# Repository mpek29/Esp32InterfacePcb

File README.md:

# Esp32InterfacePcb

# UsbUartBridge

## 🚀 Overview

**Esp32InterfacePCB** is an open-source PCB designed to provide a reliable interface between an **Espressif ESP32-WROOM-32E** module and various external modules using **JST-SM & JST-SH connectors**. This PCB simplifies ESP32 integration into embedded, IoT, and home automation projects.

## 🎯 Purpose

- 🔌 **Modular Interface**: Facilitates the connection between an ESP32-WROOM-32E and other peripherals.
- 📏 **Compact & Optimized Design**: Suitable for embedded project constraints.
- 🛠️ **Open-source & Customizable**: Modify and adapt the design to fit your specific needs.

## 📝 Features

| 🏷️ Feature            | 🔍 Description                                                 |
| ---------------------- | -------------------------------------------------------------- |
| 🔌 **ESP32 Interface** | Compatible with the ESP32-WROOM-32E module                     |
| 📡 **Connectors**      | JST-SM & JST-SH for easy connections                           |
| ⚡ **Power Supply**     | Supports 3.3V                                                  |
| 🛠️ **GPIO Access**    | Access to key GPIO pins for seamless integration               |
| 🔧 **Capacitors**      | Decoupling capacitors for signal stability                     |
| 🖥️ **PCB Design**     | Open-source & customizable                                     |
| 🌍 **Use Cases**       | IoT, embedded systems, automation, robotics, rapid prototyping |

## 📐 PCB Design Preview
| 📜 Schematic | 🖥️ PCB Layout | 🏗️ 3D |
|-----------|-----------|-----------|
|  |  |  |

## 🌟 License

This project is open-source. Feel free to use, modify, and contribute! 🚀

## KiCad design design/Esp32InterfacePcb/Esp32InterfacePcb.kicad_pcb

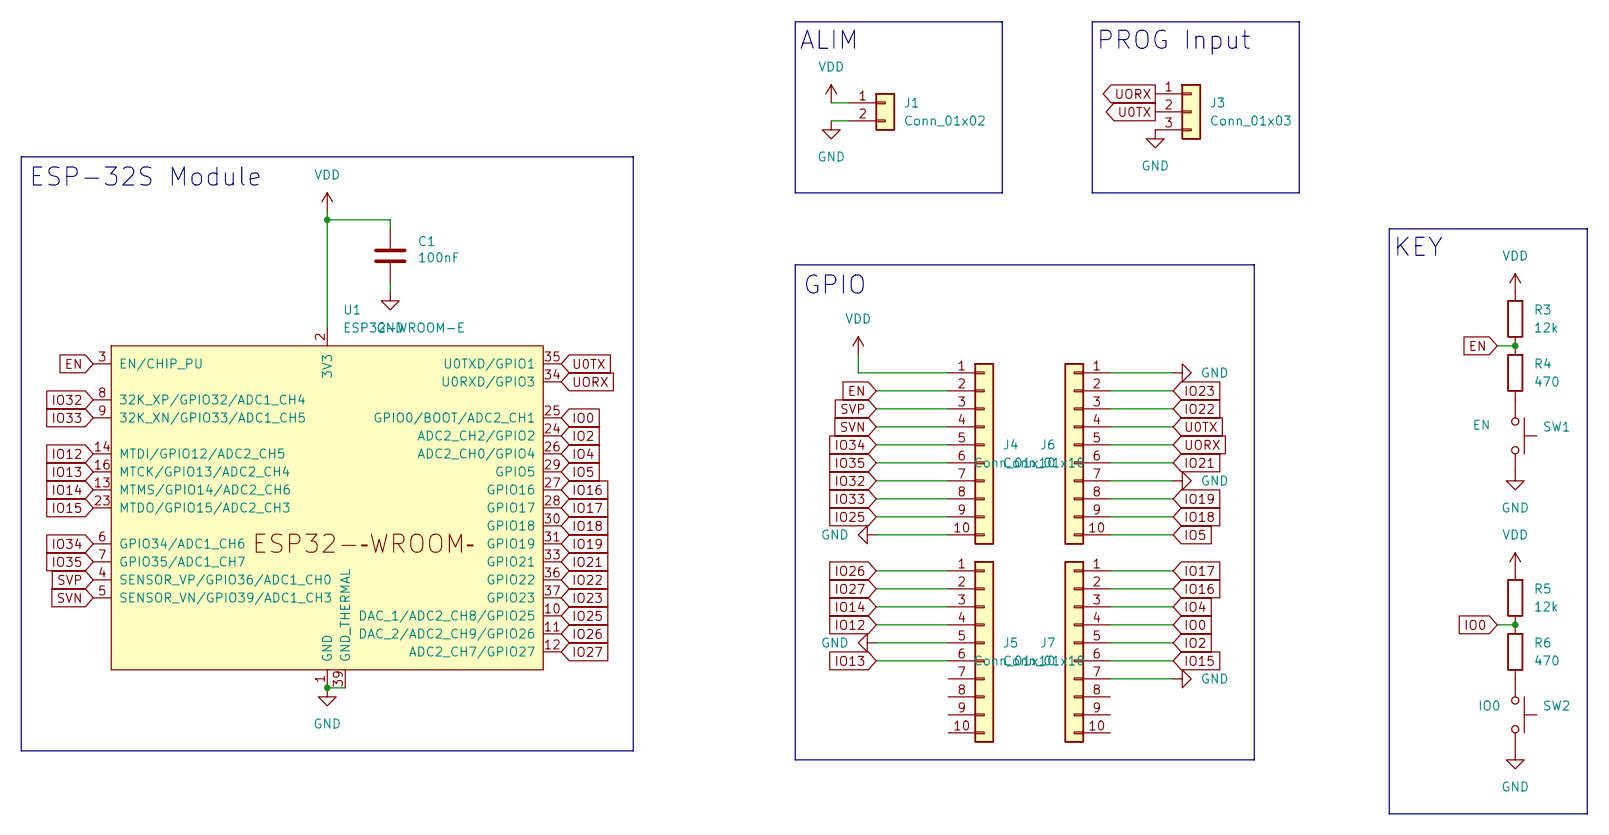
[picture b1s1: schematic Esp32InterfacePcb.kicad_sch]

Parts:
C1: 100nF; C_0603_1608Metric_Pad1.08x0.95mm_HandSolder
J1: Conn_01x02; JST_PH_S2B-PH-SM4-TB_1x02-1MP_P2.00mm_Horizontal
J3: Conn_01x03; JST_SH_SM03B-SRSS-TB_1x03-1MP_P1.00mm_Horizontal
J4, J5, J6, J7: Conn_01x10; JST_SH_SM10B-SRSS-TB_1x10-1MP_P1.00mm_Horizontal
R3, R5: 12k; R_0603_1608Metric_Pad0.98x0.95mm_HandSolder
R4, R6: 470; R_0603_1608Metric_Pad0.98x0.95mm_HandSolder
SW1: EN; SW_Push_1P1T_XKB_TS-1187A
SW2: IO0; SW_Push_1P1T_XKB_TS-1187A
U1: ESP32-WROOM-E; ESP32-WROOM-32E

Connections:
EN: J4.2, R3.1, R4.2, U1.3 (EN/CHIP_PU)
GND: C1.2, J1.2, J3.3, J4.10, J5.5, J6.1, J6.7, J7.7, SW1.2, SW2.2, U1.1 (GND), U1.15 (GND), U1.38 (GND), U1.39 (GND_THERMAL)
IO0: J7.4, R5.1, R6.2, U1.25 (GPIO0/BOOT/ADC2_CH1)
IO2: J7.5, U1.24 (ADC2_CH2/GPIO2)
IO4: J7.3, U1.26 (ADC2_CH0/GPIO4)
IO5: J6.10, U1.29 (GPIO5)
IO12: J5.4, U1.14 (MTDI/GPIO12/ADC2_CH5)
IO13: J5.6, U1.16 (MTCK/GPIO13/ADC2_CH4)
IO14: J5.3, U1.13 (MTMS/GPIO14/ADC2_CH6)
IO15: J7.6, U1.23 (MTDO/GPIO15/ADC2_CH3)
IO16: J7.2, U1.27 (GPIO16)
IO17: J7.1, U1.28 (GPIO17)
IO18: J6.9, U1.30 (GPIO18)
IO19: J6.8, U1.31 (GPIO19)
IO21: J6.6, U1.33 (GPIO21)
IO22: J6.3, U1.36 (GPIO22)
IO23: J6.2, U1.37 (GPIO23)
IO25: J4.9, U1.10 (DAC_1/ADC2_CH8/GPIO25)
IO26: J5.1, U1.11 (DAC_2/ADC2_CH9/GPIO26)
IO27: J5.2, U1.12 (ADC2_CH7/GPIO27)
IO32: J4.7, U1.8 (32K_XP/GPIO32/ADC1_CH4)
IO33: J4.8, U1.9 (32K_XN/GPIO33/ADC1_CH5)
IO34: J4.5, U1.6 (GPIO34/ADC1_CH6)
IO35: J4.6, U1.7 (GPIO35/ADC1_CH7)
unnamed: R4.1, SW1.1
unnamed: R6.1, SW2.1
SVN: J4.4, U1.5 (SENSOR_VN/GPIO39/ADC1_CH3)
SVP: J4.3, U1.4 (SENSOR_VP/GPIO36/ADC1_CH0)
U0TX: J3.2, J6.4, U1.35 (U0TXD/GPIO1)
UORX: J3.1, J6.5, U1.34 (U0RXD/GPIO3)
VDD: C1.1, J1.1, J4.1, R3.2, R5.2, U1.2 (3V3)

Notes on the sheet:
KEY
ALIM
GPIO
ESP-32S Module
PROG Input

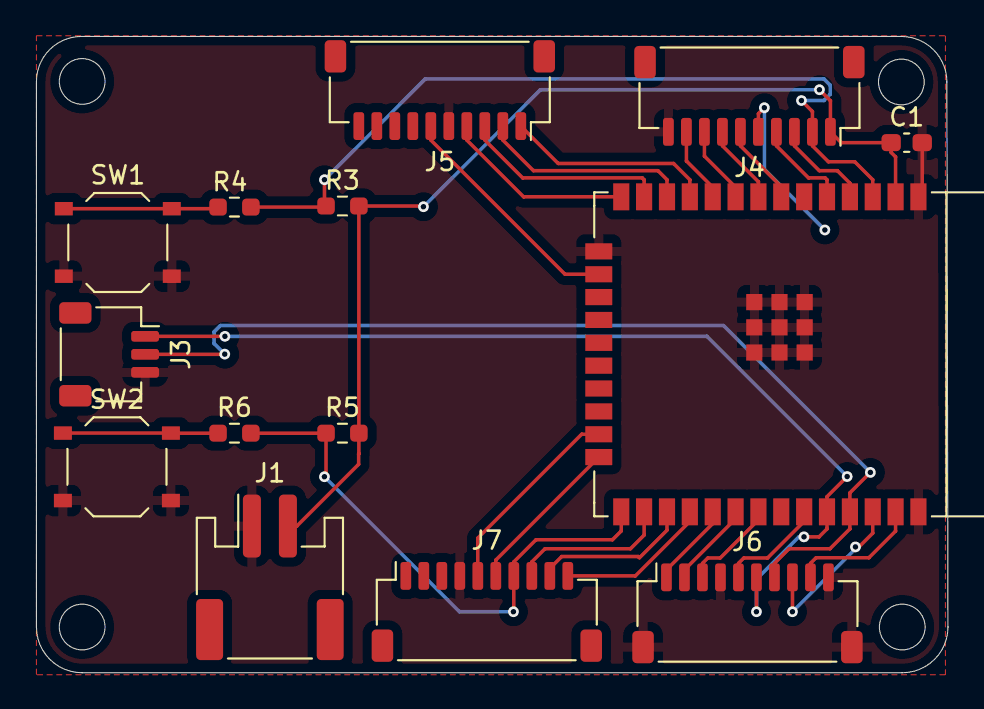
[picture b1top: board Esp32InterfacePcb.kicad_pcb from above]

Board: 2 copper layers, 50.6 x 35.3 mm, 14 parts (0 on the bottom side), 31 nets.

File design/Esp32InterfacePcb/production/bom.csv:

Designator,Footprint,Quantity,Value,LCSC Part #
C1,0603,1,100nF,
J1,JST_PH_S2B-PH-SM4-TB_1x02-1MP_P2.00mm_Horizontal,1,Conn_01x02,
J3,JST_SH_SM03B-SRSS-TB_1x03-1MP_P1.00mm_Horizontal,1,Conn_01x03,
"J4, J5, J6, J7",JST_SH_SM10B-SRSS-TB_1x10-1MP_P1.00mm_Horizontal,4,Conn_01x10,
"R3, R5",0603,2,12k,
"R4, R6",0603,2,470,
SW1,SW_Push_1P1T_XKB_TS-1187A,1,EN,
SW2,SW_Push_1P1T_XKB_TS-1187A,1,IO0,
U1,ESP32-WROOM-32E,1,ESP32-WROOM-E,

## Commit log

2025-03-02 valid scheme
2025-03-03 best adaptation to adafruit swirly grill
2025-03-03 edit pic
2025-04-10 adjustement and gerber files
